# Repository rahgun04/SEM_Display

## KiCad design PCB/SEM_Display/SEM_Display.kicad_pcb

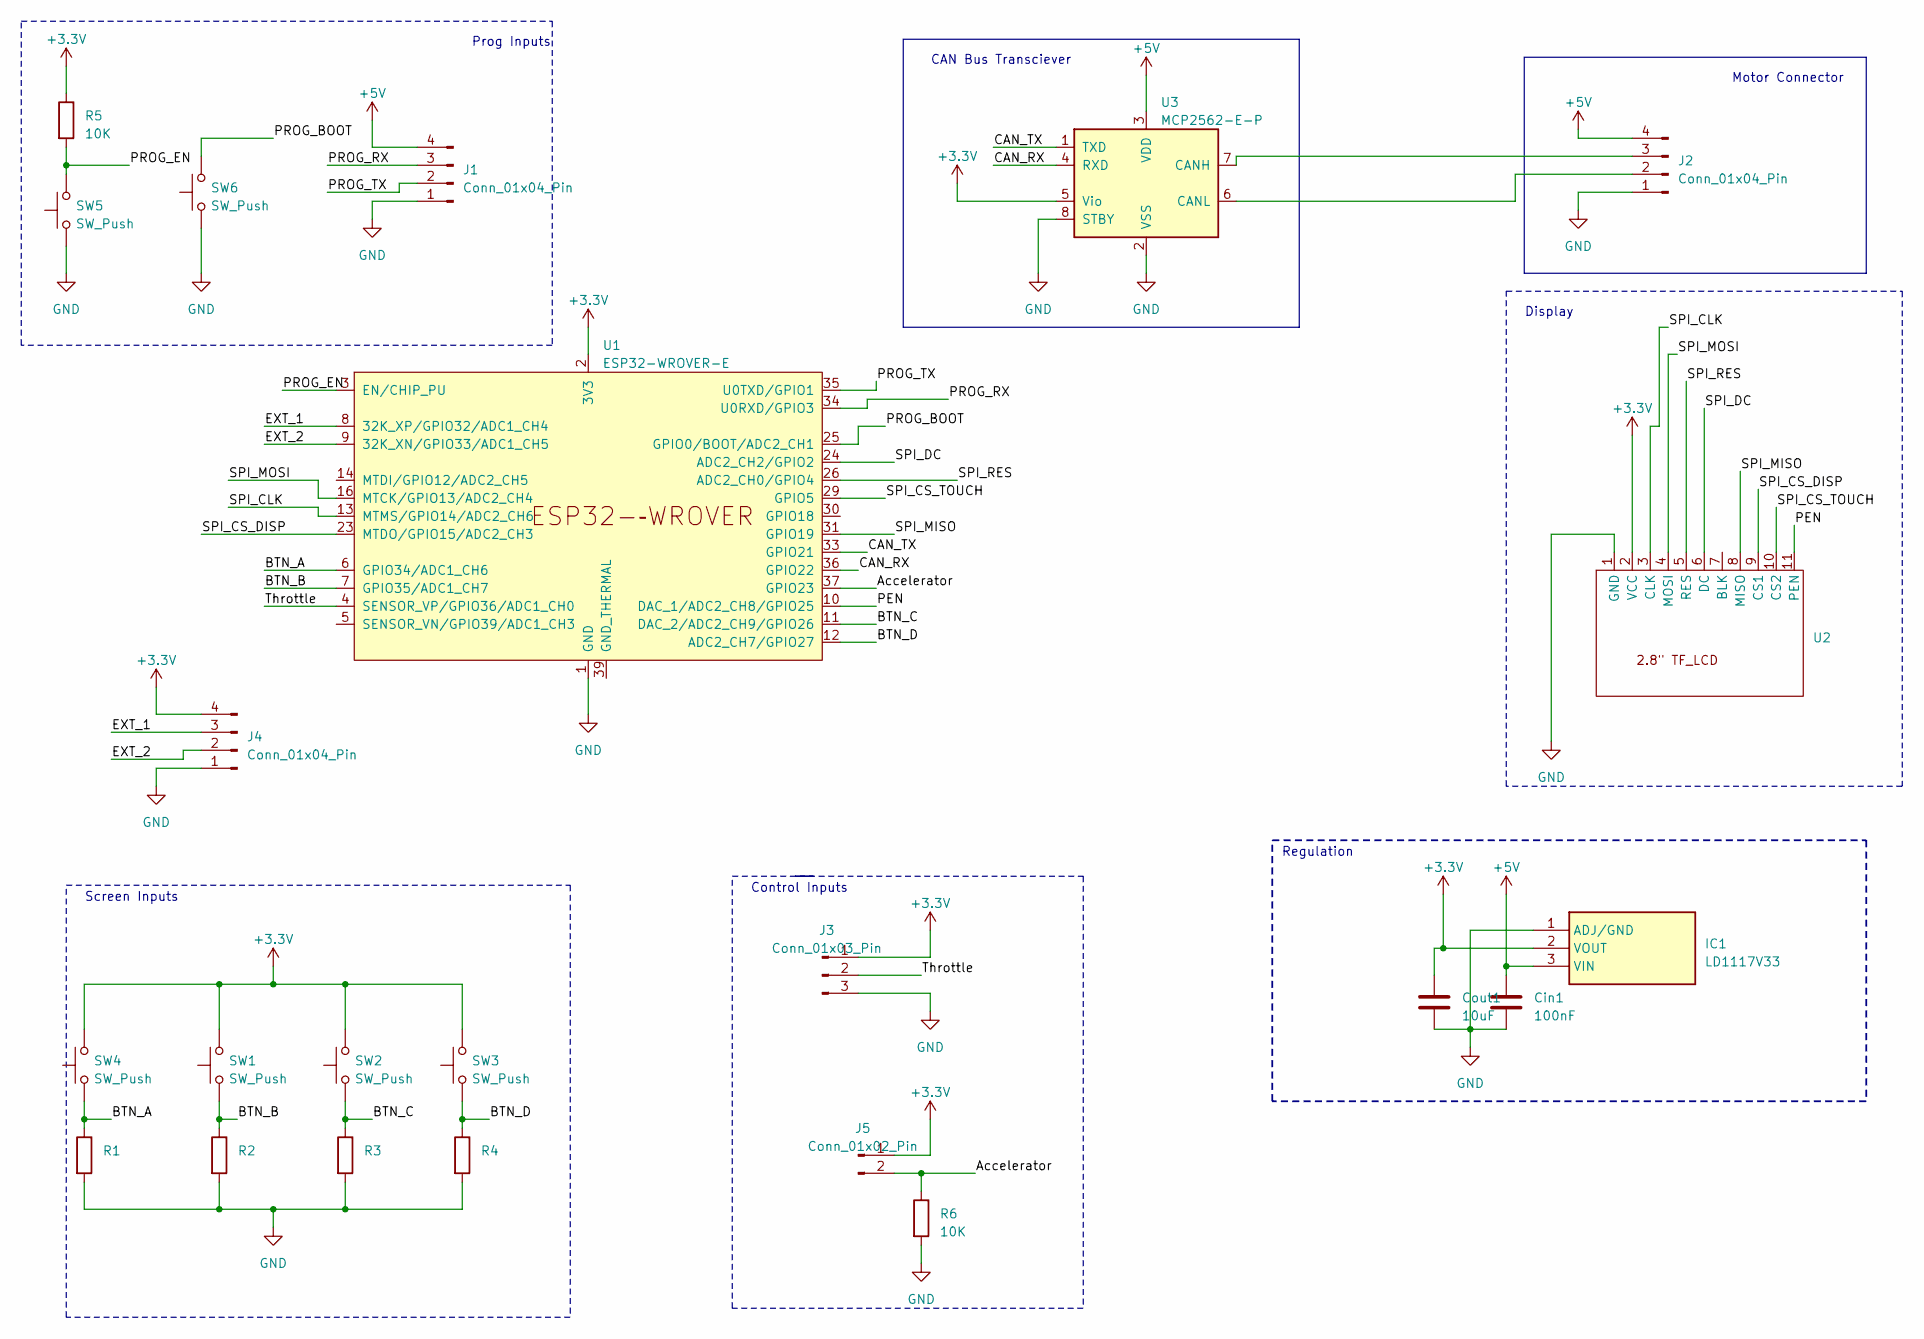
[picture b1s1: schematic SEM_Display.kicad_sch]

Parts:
Cin1: 100nF; C_Rect_L7.0mm_W3.5mm_P5.00mm
Cout1: 10uF; CP_Radial_D5.0mm_P2.00mm
IC1: LD1117V33; TO255P460X1020X2008-3P; Manufacturer_Part_Number LD1117V33
J1, J2, J4: Conn_01x04_Pin; PinHeader_1x04_P2.54mm_Horizontal
J3: Conn_01x03_Pin; PinHeader_1x03_P2.54mm_Horizontal
J5: Conn_01x02_Pin; PinHeader_1x02_P2.54mm_Horizontal
R1, R2, R3, R4, R5, R6: 10K; R_Axial_DIN0207_L6.3mm_D2.5mm_P7.62mm_Horizontal
SW1, SW2, SW3, SW4, SW5, SW6: SW_Push; SW_PUSH_6mm_H5mm
U1: ESP32-WROVER-E
U2: ILI9341
U3: MCP2562-E-P; DIP-8_W7.62mm

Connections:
+3.3V: Cout1.1, IC1.2 (VOUT), J3.1, J4.4, J5.1, R5.1, SW1.2, SW2.2, SW3.2, SW4.2, U1.2 (3V3), U2.2 (VCC), U3.5 (Vio)
+5V: Cin1.1, IC1.3 (VIN), J1.4, J2.4, U3.3 (VDD)
/Accelerator: J5.2, R6.1, U1.37 (GPIO23)
/BTN_A: R1.1, SW4.1, U1.6 (GPIO34/ADC1_CH6)
/BTN_B: R2.1, SW1.1, U1.7 (GPIO35/ADC1_CH7)
/BTN_C: R3.1, SW2.1, U1.11 (DAC_2/ADC2_CH9/GPIO26)
/BTN_D: R4.1, SW3.1, U1.12 (ADC2_CH7/GPIO27)
/CAN_RX: U1.36 (GPIO22), U3.4 (RXD)
/CAN_TX: U1.33 (GPIO21), U3.1 (TXD)
/EXT_1: J4.3, U1.8 (32K_XP/GPIO32/ADC1_CH4)
/EXT_2: J4.2, U1.9 (32K_XN/GPIO33/ADC1_CH5)
/PEN: U1.10 (DAC_1/ADC2_CH8/GPIO25), U2.11 (PEN)
/PROG_BOOT: SW6.2, U1.25 (GPIO0/BOOT/ADC2_CH1)
/PROG_EN: R5.2, SW5.2, U1.3 (EN/CHIP_PU)
/PROG_RX: J1.3, U1.34 (U0RXD/GPIO3)
/PROG_TX: J1.2, U1.35 (U0TXD/GPIO1)
/SPI_CLK: U1.13 (MTMS/GPIO14/ADC2_CH6), U2.3 (CLK)
/SPI_CS_DISP: U1.23 (MTDO/GPIO15/ADC2_CH3), U2.9 (CS1)
/SPI_CS_TOUCH: U1.29 (GPIO5), U2.10 (CS2)
/SPI_DC: U1.24 (ADC2_CH2/GPIO2), U2.6 (DC)
/SPI_MISO: U1.31 (GPIO19), U2.8 (MISO)
/SPI_MOSI: U1.16 (MTCK/GPIO13/ADC2_CH4), U2.4 (MOSI)
/SPI_RES: U1.26 (ADC2_CH0/GPIO4), U2.5 (RES)
/Throttle: J3.2, U1.4 (SENSOR_VP/GPIO36/ADC1_CH0)
GND: Cin1.2, Cout1.2, IC1.1 (ADJ/GND), J1.1, J2.1, J3.3, J4.1, R1.2, R2.2, R3.2, R4.2, R6.2, SW5.1, SW6.1, U1.1 (GND), U1.15 (GND), U1.38 (GND), U2.1 (GND), U3.2 (VSS), U3.8 (STBY)
unnamed: J2.2, U3.6 (CANL)
unnamed: J2.3, U3.7 (CANH)

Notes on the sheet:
Motor Connector
Regulation
Control Inputs
Screen Inputs
Prog Inputs
Display
CAN Bus Transciever

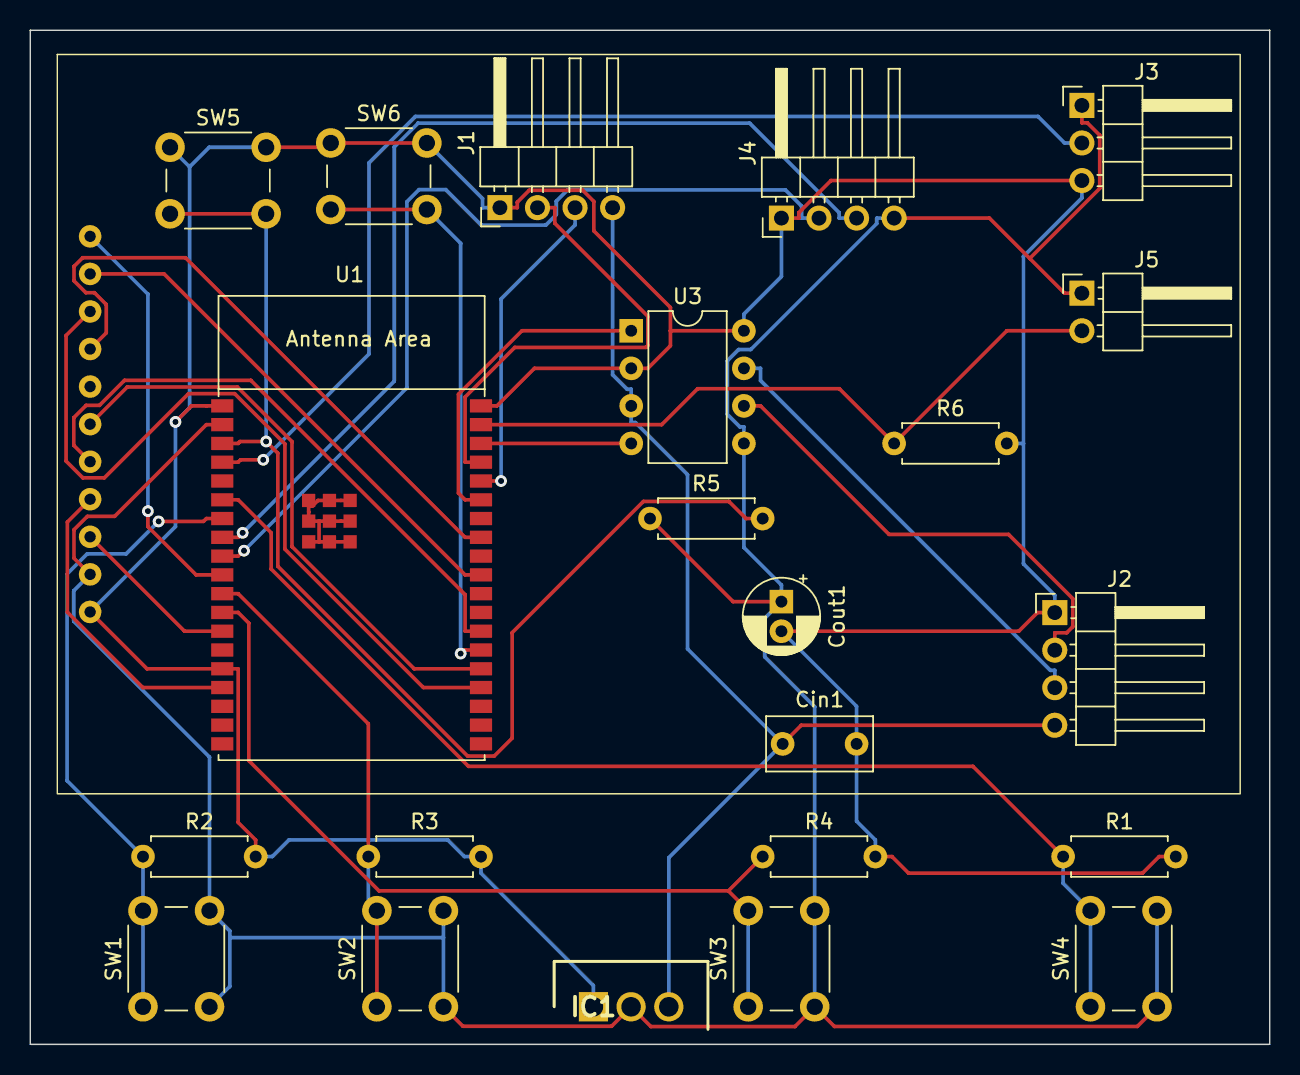
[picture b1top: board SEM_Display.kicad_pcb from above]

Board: 2 copper layers, 83.8 x 68.6 mm, 23 parts (0 on the bottom side), 27 nets.

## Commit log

2023-04-02 PCB, Example Code
2023-04-03 Converted Global Dependencies into local ones
2023-04-06 (kicad-libraries-esp32) Included ESP32 symbols and footprints
2023-04-06 Create kicad-libraries-esp32
2023-04-06 esp32 footprints
2023-04-06 Included esp32 footprints
